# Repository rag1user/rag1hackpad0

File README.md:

# Rag's macropad with 4 switches and 2 LEDs and additional LED controller/strip

This is my first blueprint project. I started out with a just modest change (to add a Neopixel_txt) on top of the instructions provided, but revised it based on feedback
Here is what I have in revision2:
1. The macropad has 4 keys similar to most other starter macropad projects
2. In addition, the macropad also has a SW coded switch (Surface mount SH-7010) that can be used to do additional controlls such as scrolling, volume up/down, screen brigntness up/down
3. I also added a low-end SHT1x temperature and humidity sensor out of curiosity (I want to play with more sensor projects in future and can't resist putting one right away although it makes little sense to have a sensor in a macropad/ hackpad)

The 4 keys will function as:

key1: gives a help message on what keys2,3,4 do

key2: performs \<ALT\>\<tab\> with delay b/w switching

key2: performs \<CTL\>\<tab\> with delay b/w switching

key2: performs \<WIN\>\<tab\> with delay b/w switching

Rotary key will be used for scrolling, volume controll and screen brigntness control functions (activated by  keys2-4) (Firmware for this is pending update)

LED1: Lights up when board is ready for use (keeps blinking or turned off on error)

LED2: Blinks whenever a key is pressed

SHT1x sensor: Provides temperature and humidity measurement (no display; will have to extract this via RP2040)

# Finished product (minus switches):

# PCB layout

# Schematic

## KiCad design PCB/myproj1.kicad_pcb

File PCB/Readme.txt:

# This file has the PCB Design files. This includes the .kicadpro, .kicadsch, and .kicad_pcb files

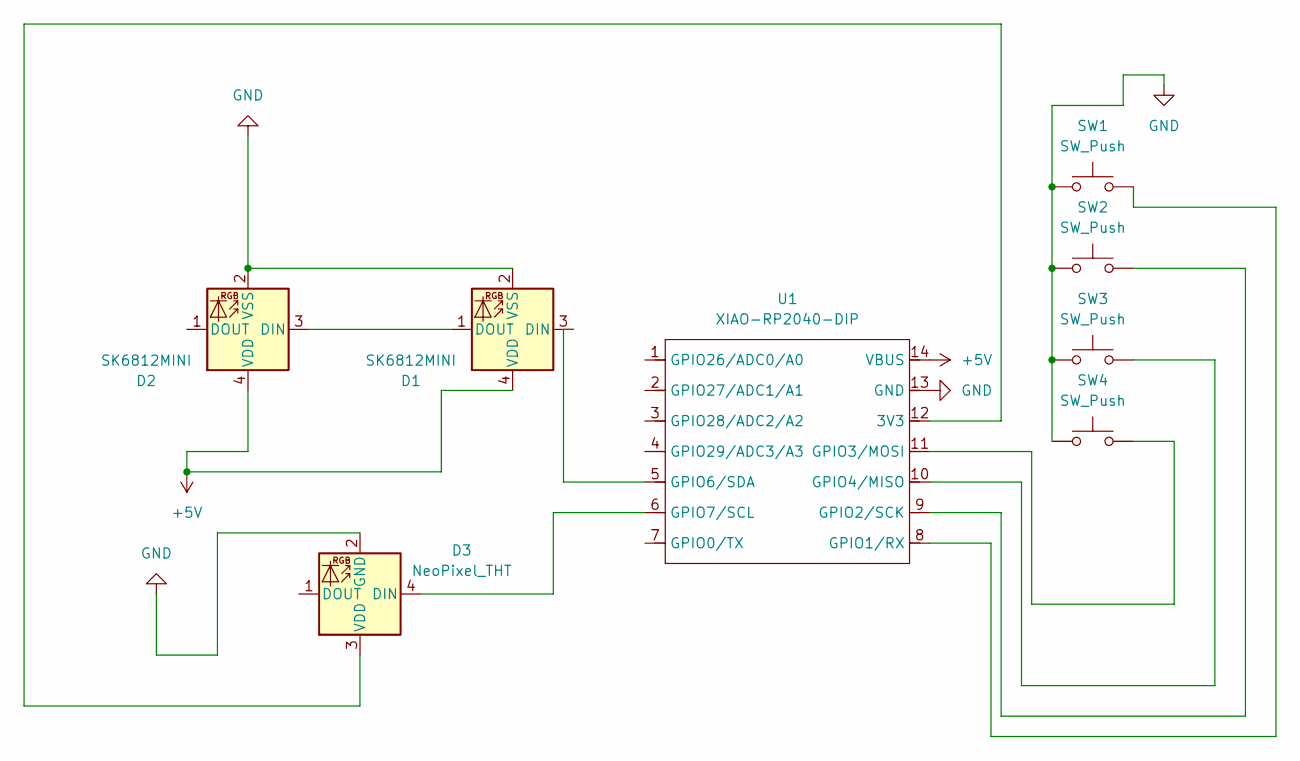
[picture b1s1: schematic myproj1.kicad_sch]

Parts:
D1, D2: SK6812MINI; LED_SK6812MINI_PLCC4_3.5x3.5mm_P1.75mm
D3: NeoPixel_THT; LED_WS2812B-2020_PLCC4_2.0x2.0mm
SW1, SW2, SW3, SW4: SW_Push; SW_Cherry_MX_1.00u_PCB
U1: XIAO-RP2040-DIP

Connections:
+5V: D1.4 (VDD), D2.4 (VDD), U1.14 (VBUS)
GND: D1.2 (VSS), D2.2 (VSS), D3.2 (GND), SW1.1, SW2.1, SW3.1, SW4.1, U1.13 (GND)
unnamed: D1.3 (DIN), U1.5 (GPIO6/SDA)
unnamed: D1.1 (DOUT), D2.3 (DIN)
unnamed: D3.4 (DIN), U1.6 (GPIO7/SCL)
unnamed: D3.3 (VDD), U1.12 (3V3)
unnamed: SW1.2, U1.8 (GPIO1/RX)
unnamed: SW2.2, U1.9 (GPIO2/SCK)
unnamed: SW4.2, U1.11 (GPIO3/MOSI)
unnamed: SW3.2, U1.10 (GPIO4/MISO)

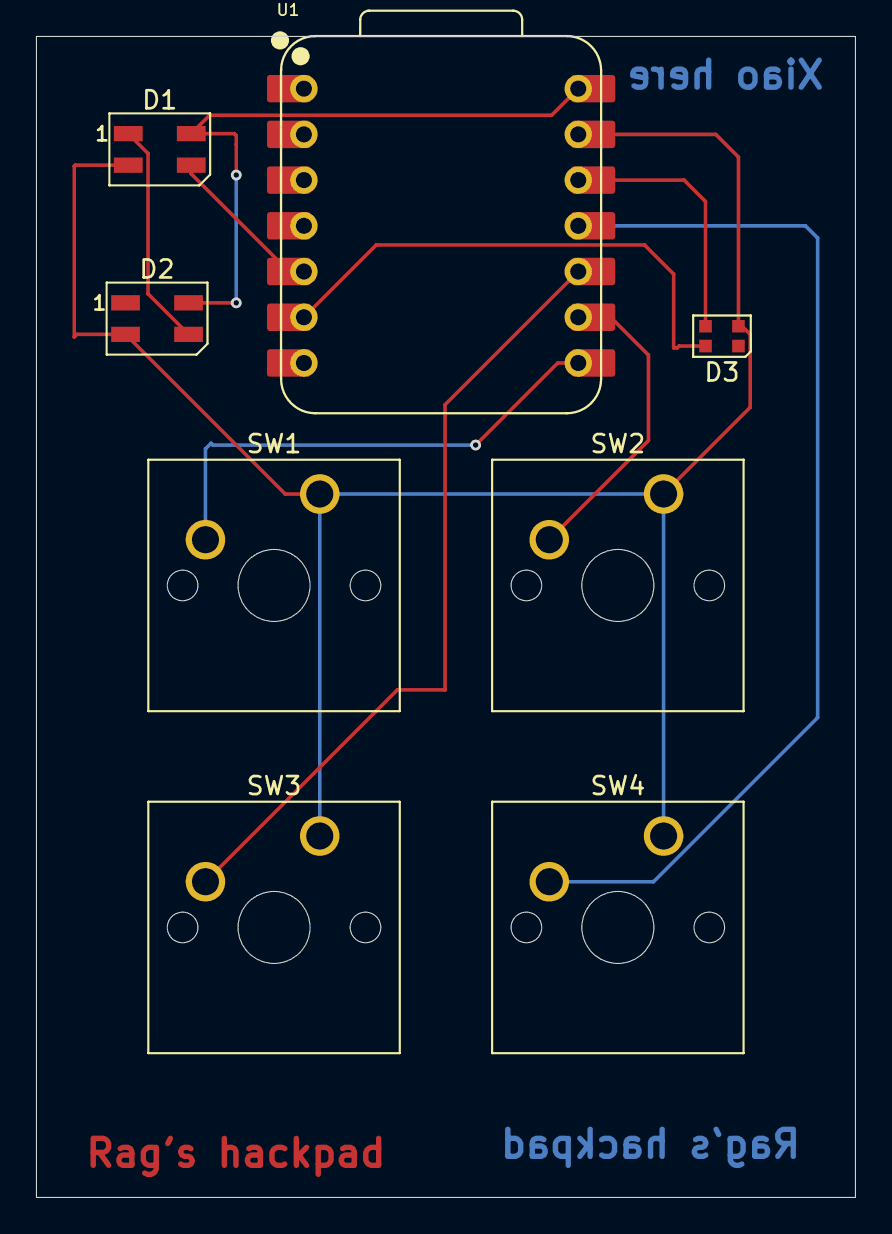
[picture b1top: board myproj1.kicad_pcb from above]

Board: 2 copper layers, 45.5 x 64.5 mm, 8 parts (0 on the bottom side), 10 nets.

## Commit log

2025-11-18 second commit
2025-11-18 third commit, accidentally lined up my electronics wrong :(
2025-11-18 fourth commit, why did it not freakin save
2025-11-18 Create README.md for SinnerPad project
    Added initial README with project details and features.
2025-11-19 Add images to README for enhanced documentation
    Added additional images to the README for better visualization.
2025-11-19 finished
2025-12-04 Update README.md
    Revision2 of the project with changes suggested to get rid of Neopixel_txt
